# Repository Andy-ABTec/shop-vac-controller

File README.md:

# Shop Vac Controller

An Arduino Nano-based project to provide automatic control for a small workshop vacuum by either sensing tool use, or by a keyfob style remote control.

Four LEDs display the status of the controller and its trigger source. It should be noted that the "Vac On" LED flashes if a startup or shutdown delay is in progress.

 Power control for the vacuum is provided by a 20A solid state relay and the remote control by a small keyfob and receiver ( I used a [**fob/receiver** from Amazon](https://www.amazon.co.uk/gp/product/B08SHQ749R/)).

Power-tool on/off sensing is provided by a small circuit by [**0033mer**](https://www.youtube.com/user/0033mer) using a cheap current transformer  I found on [**YouTube**](https://www.youtube.com/watch?v=gvBVxQGS_OU&t=280s).

Both the *sensitivity* of the current sensor and the turn-off delay for the vacuum control relay are adjustable by preset potentiometers.

Whilst the remote has no turn-on delay, the vacuum turns on 3s after the power tool is started (this setting may be adjusted in the Arduino code). This delay helps to reduce the excessive surge current created if both the power tool and the vacuum are turned on together.

The turn-off delay is the same for both the power tool and the remote fob, and can easily be adjusted between 3s and 30s with a preset potentiometer, this allows time for the wood chips and sawdust to be cleared from the vacuum hose.

It should be noted that if the vacuum is initiated by the mains-powered tool turning on, it can only be turned off by stopping the tool, and, in a similar way, if initiated by the remote fob it can only be turned off by the remote fob.

The vacuum power circuit should include a suitable fuse.

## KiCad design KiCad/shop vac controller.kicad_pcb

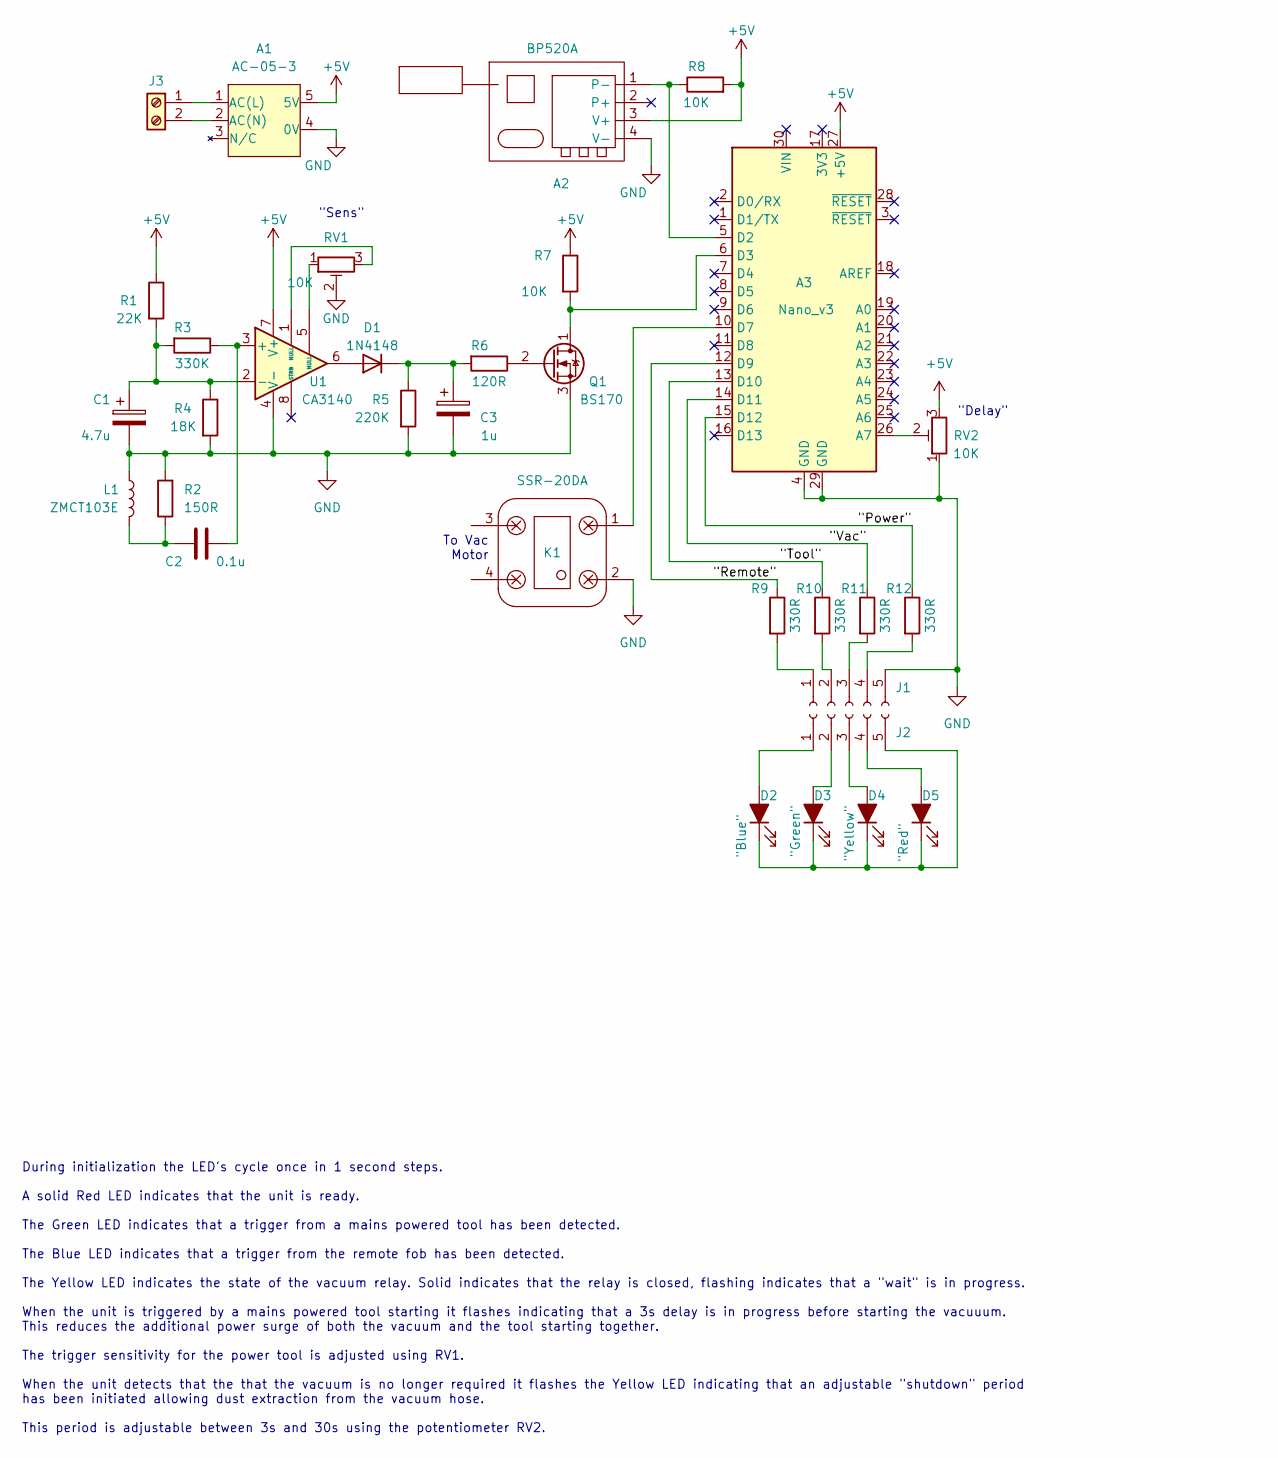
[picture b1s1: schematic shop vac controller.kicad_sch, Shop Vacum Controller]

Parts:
A1: AC-05-3
A2: BP520A
A3: Nano_v3; Arduino_Nano
C1: 4.7u; C_Radial_D5.0mm_H11.0mm_P2.00mm
C2: 0.1u; C_Disc_D5.1mm_W3.2mm_P5.00mm
C3: 1u; C_Radial_D4.0mm_H7.0mm_P1.50mm
D1: 1N4148; D_DO-35_SOD27_P7.62mm_Horizontal
D2: "Blue"; LED_D3.0mm
D3: "Green"; LED_D3.0mm
D4: "Yellow"; LED_D3.0mm
D5: "Red"; LED_D3.0mm
J1, J2: Conn_01x05_Socket; 5 pin jumper
J3: Screw_Terminal_01x02; TerminalBlock_bornier-2_P5.08mm
K1: SSR-20DA; TerminalBlock_bornier-2_P5.08mm
L1: ZMCT103E
Q1: BS170; TO-92_Inline
R1: 22K; R_Axial_DIN0204_L3.6mm_D1.6mm_P7.62mm_Horizontal
R2: 150R; R_Axial_DIN0204_L3.6mm_D1.6mm_P7.62mm_Horizontal
R3: 330K; R_Axial_DIN0204_L3.6mm_D1.6mm_P7.62mm_Horizontal
R4: 18K; R_Axial_DIN0204_L3.6mm_D1.6mm_P7.62mm_Horizontal
R5: 220K; R_Axial_DIN0204_L3.6mm_D1.6mm_P7.62mm_Horizontal
R6: 120R; R_Axial_DIN0204_L3.6mm_D1.6mm_P7.62mm_Horizontal
R7, R8: 10K; R_Axial_DIN0204_L3.6mm_D1.6mm_P7.62mm_Horizontal
R9, R10, R11, R12: 330R; R_Axial_DIN0204_L3.6mm_D1.6mm_P7.62mm_Horizontal
RV1, RV2: 10K; Potentiometer_Runtron_RM-065_Vertical
U1: CA3140; DIP-8_W7.62mm

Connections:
+5V: A1.5 (5V), A2.3 (V+), A3.27 (+5V), R1.1, R7.1, R8.2, RV2.3, U1.7 (V+)
/"Power": A3.15 (D12), R12.1
/"Remote": A3.12 (D9), R9.1
/"Tool": A3.13 (D10), R10.1
/"Vac": A3.14 (D11), R11.1
GND: A1.4 (0V), A2.4 (V-), A3.4 (GND), A3.29 (GND), C1.2, C3.2, J1.5, K1.2, L1.1, Q1.3 (S), R2.2, R4.2, R5.2, RV1.2, RV2.1, U1.4 (V-)
unnamed: A1.1 (AC(L)), J3.1
unnamed: A1.2 (AC(N)), J3.2
unnamed: A2.1 (P-), A3.5 (D2), R8.1
unnamed: A3.26 (A7), RV2.2
unnamed: A3.6 (D3), Q1.1 (D), R7.2
unnamed: A3.10 (D7), K1.1
unnamed: C2.1, L1.2, R2.1
unnamed: D1.2 (A), U1.6
unnamed: C3.1, D1.1 (K), R5.1, R6.2
unnamed: D2.2 (A), J2.1
unnamed: D2.1 (K), D3.1 (K), D4.1 (K), D5.1 (K), J2.5
unnamed: D3.2 (A), J2.2
unnamed: D4.2 (A), J2.3
unnamed: D5.2 (A), J2.4
unnamed: J1.1, R9.2
unnamed: J1.2, R10.2
unnamed: J1.3, R11.2
unnamed: J1.4, R12.2
unnamed: Q1.2 (G), R6.1
unnamed: RV1.1, U1.5 (NULL)
unnamed: RV1.3, U1.1 (NULL)
unnamed: C2.2, R3.1, U1.3 (+)
unnamed: C1.1, R1.2, R3.2, R4.1, U1.2 (-)

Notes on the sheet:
During initialization the LED's cycle once in 1 second steps. A solid Red LED indicates that the unit is ready. The Green LED indicates that a trigger from a mains powered tool has been detected. The Blue LED indicates that a trigger from the remote fob has been detected. The Yellow LED indicates t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
To Vac Motor
"Delay"
"Sens"

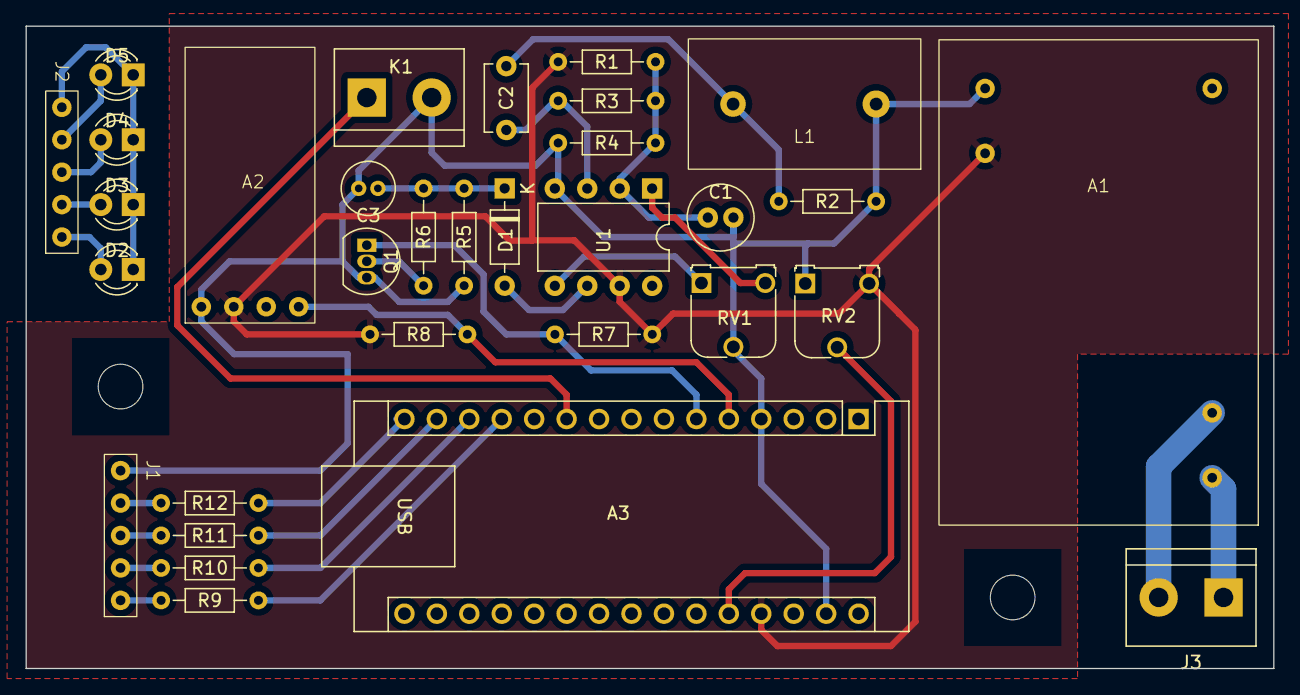
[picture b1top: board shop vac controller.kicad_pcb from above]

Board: 2 copper layers, 97.7 x 50.3 mm, 32 parts (0 on the bottom side), 29 nets.

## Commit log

2022-05-22 update code
2022-05-22 rebuilding code
2022-05-26 updated main.cpp
2022-06-01 main.cpp updated
2022-06-01 Updated Schematic
2022-06-01 updated link to schematic for v1.4
2022-06-05 update readme schemativ
2022-06-08 update lint and PrintF
2022-07-16 update spelling/syntax
2022-12-17 spelling and syntax fixes
2022-12-17 linting
2022-12-29 Create shop-vac-controller.code-workspace
2023-04-29 online backup?
2023-07-13 updates
    updates
2023-09-14 Update main.cpp
    test led for relay
2024-01-18 circuit update
    circuit update
2024-01-29 debug on
2024-01-29 Spelling
2024-11-14 KiCAD include
    Include the live KiCAD files?
2024-11-14 KiCAD update
2024-11-22 confused
2024-11-23 confusded
2024-11-23 ignore kicad backups
2024-12-06 schematic text update
2024-12-28 Update README.md
    Added schematic image
2024-12-29 changes?
